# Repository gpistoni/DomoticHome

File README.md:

# DomoticHome
DomoticHome

Arduino personal Net

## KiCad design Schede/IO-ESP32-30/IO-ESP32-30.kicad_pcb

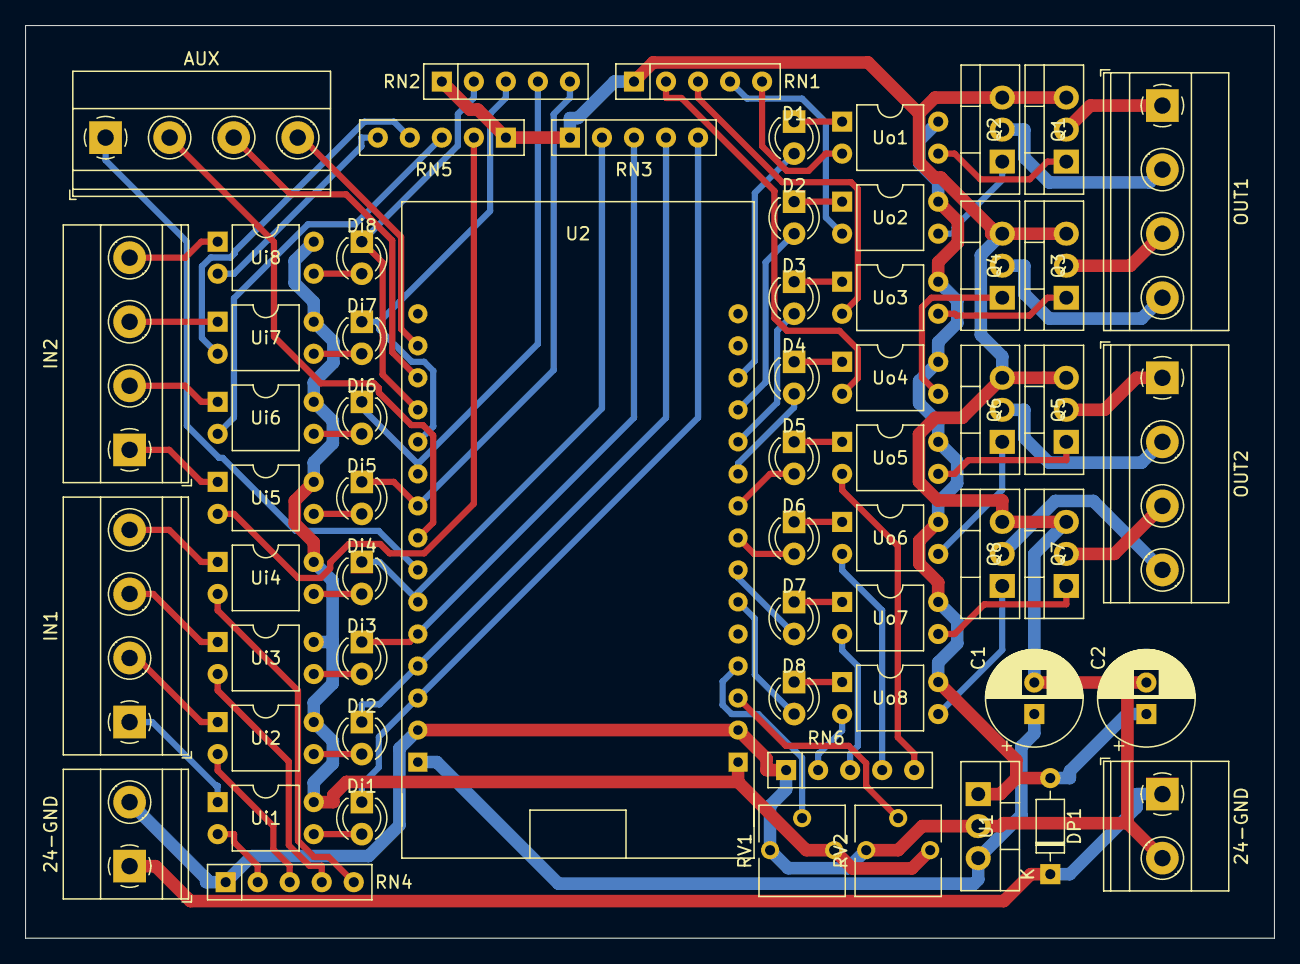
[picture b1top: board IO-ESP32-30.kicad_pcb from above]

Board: 2 copper layers, 99.1 x 72.4 mm, 60 parts (0 on the bottom side), 83 nets.

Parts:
24-GND, 24-GND#2: Screw_Terminal_01x02; TerminalBlock_Phoenix_MKDS-1,5-2-5.08_1x02_P5.08mm_Horizont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
AUX: Screw_Terminal_01x04; TerminalBlock_Phoenix_MKDS-1,5-4-5.08_1x04_P5.08mm_Horizont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
C1: 10uf; CP_Radial_D7.5mm_P2.50mm
C2: 100uf; CP_Radial_D7.5mm_P2.50mm
D1, D2, D3, D4, D5, D6, D7, D8: LED; LED_D3.0mm
DP1: DIODE; D_DO-35_SOD27_P7.62mm_Horizontal
Di1, Di2, Di3, Di4, Di5, Di6, Di7, Di8: LED; LED_D3.0mm
IN1, IN2: Screw_Terminal_01x04; TerminalBlock_Phoenix_MKDS-1,5-4-5.08_1x04_P5.08mm_Horizont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
OUT1, OUT2: Screw_Terminal_01x04; TerminalBlock_Phoenix_MKDS-1,5-4-5.08_1x04_P5.08mm_Horizont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
Q1, Q2, Q3, Q4, Q5, Q6, Q7, Q8: IRF540N; TO-220-3_Vertical
RN1, RN6: R_220; R_Array_SIP5
RN2, RN4: R_2k; R_Array_SIP5
RN3, RN5: R_1k; R_Array_SIP5
RV1, RV2: R_POT_10k; Potentiometer_Vishay_T73YP_Vertical
U1: L7805; TO-220-3_Vertical
U2: DOIT-ESP32-30PIN; ESP32-DOIT-DEVKIT
Ui1, Ui2, Ui3, Ui4, Ui5, Ui6, Ui7, Ui8: PS2501; DIP-4_W7.62mm
Uo1, Uo2, Uo3, Uo4, Uo5, Uo6, Uo7, Uo8: PS2501; DIP-4_W7.62mm

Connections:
+3V3: RV1.1, RV2.1, U2.16, Ui1.4, Ui2.4, Ui3.4, Ui4.4, Ui5.4, Ui6.4, Ui7.4, Ui8.4
+5V: C1.1, U1.3, U2.15
+24V: C2.1, DP1.2, U1.1, Uo1.4, Uo2.4, Uo3.4, Uo4.4, Uo5.4, Uo6.4, Uo7.4, Uo8.4
/P1: OUT1.1, Q1.2
/P2: OUT1.2, Q2.2
/P3: OUT1.3, Q3.2
/P4: OUT1.4, Q4.2
/P5: OUT2.1, Q5.2
/P6: OUT2.2, Q6.2
/P7: OUT2.3, Q7.2
/P8: OUT2.4, Q8.2
GND: 24-GND.2, 24-GND#2.2, C1.2, C2.2, Q1.3, Q2.3, Q3.3, Q4.3, Q5.3, Q6.3, Q7.3, Q8.3, RN1.1, RN2.1, RN3.1, RN4.1, RN5.1, RN6.1, RV1.3, RV2.3, U1.2, U2.14, U2.17
unnamed: AUX.1, U2.9
unnamed: AUX.2, U2.8
unnamed: AUX.3, U2.3
unnamed: AUX.4, U2.2
unnamed: D1.1, Uo1.1
unnamed: D1.2, U2.28
unnamed: D2.1, Uo2.1
unnamed: D2.2, U2.27
unnamed: D3.1, Uo3.1
unnamed: D3.2, U2.26
unnamed: D4.1, Uo4.1
unnamed: D4.2, U2.25
unnamed: D5.1, Uo5.1
unnamed: D5.2, U2.24
unnamed: D6.1, Uo6.1
unnamed: D6.2, U2.23
unnamed: D7.1, Uo7.1
unnamed: D7.2, U2.22
unnamed: D8.1, Uo8.1
unnamed: D8.2, U2.21
unnamed: Di1.1, RN3.5, U2.13
unnamed: Di1.2, Ui1.3
unnamed: Di2.1, RN3.4, U2.12
unnamed: Di2.2, Ui2.3
unnamed: Di3.1, RN3.3, U2.11
unnamed: Di3.2, Ui3.3
unnamed: Di4.1, RN3.2, U2.10
unnamed: Di4.2, Ui4.3
unnamed: Di5.1, RN5.5, U2.7
unnamed: Di5.2, Ui5.3
unnamed: Di6.1, RN5.4, U2.6
unnamed: Di6.2, Ui6.3
unnamed: Di7.1, RN5.3, U2.5
unnamed: Di7.2, Ui7.3
unnamed: Di8.1, RN5.2, U2.4
unnamed: Di8.2, Ui8.3
unnamed: IN1.1, Ui1.1
unnamed: IN1.2, Ui2.1
unnamed: IN1.3, Ui3.1
unnamed: IN1.4, Ui4.1
unnamed: IN2.1, Ui5.1
unnamed: IN2.2, Ui6.1
unnamed: IN2.3, Ui7.1
unnamed: IN2.4, Ui8.1
unnamed: Q1.1, Uo1.3
unnamed: Q2.1, Uo2.3
unnamed: Q3.1, Uo3.3
unnamed: Q4.1, Uo4.3
unnamed: Q5.1, Uo5.3
unnamed: Q6.1, Uo6.3
unnamed: Q7.1, Uo7.3
unnamed: Q8.1, Uo8.3
unnamed: RN1.2, Uo4.2
unnamed: RN1.3, Uo3.2
unnamed: RN1.4, Uo2.2
unnamed: RN1.5, Uo1.2
unnamed: RN2.2, Ui5.2
unnamed: RN2.3, Ui6.2
unnamed: RN2.4, Ui7.2
unnamed: RN2.5, Ui8.2
unnamed: RN4.2, Ui1.2
unnamed: RN4.3, Ui2.2
unnamed: RN4.4, Ui3.2
unnamed: RN4.5, Ui4.2
unnamed: RN6.2, Uo8.2
unnamed: RN6.3, Uo7.2
unnamed: RN6.4, Uo6.2
unnamed: RN6.5, Uo5.2
unnamed: RV1.2, U2.19
unnamed: RV2.2, U2.18
VCC: 24-GND.1, 24-GND#2.1, DP1.1

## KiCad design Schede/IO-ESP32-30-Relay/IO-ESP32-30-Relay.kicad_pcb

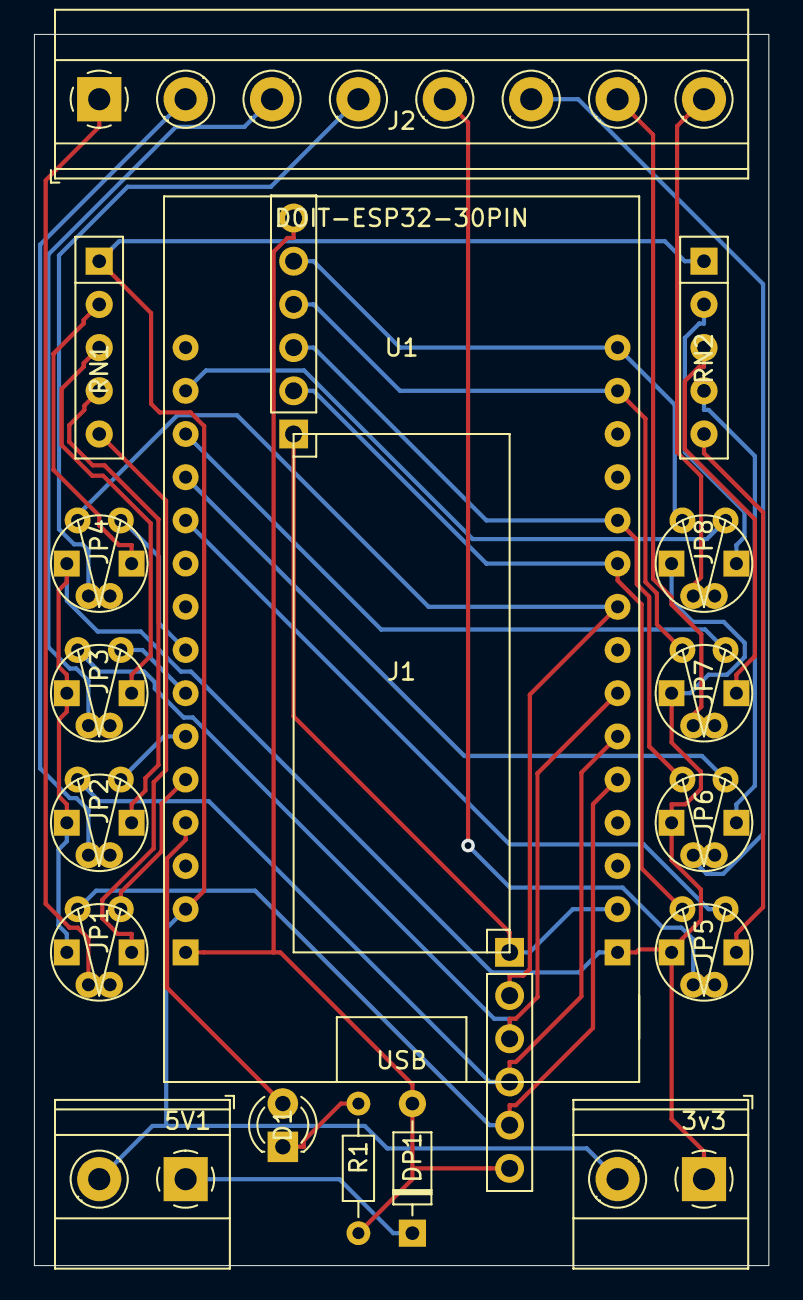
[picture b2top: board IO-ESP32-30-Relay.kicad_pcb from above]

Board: 2 copper layers, 43.2 x 72.4 mm, 18 parts (0 on the bottom side), 38 nets.

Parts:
3v3, 5V1: Screw_Terminal_01x02; TerminalBlock_Phoenix_MKDS-1,5-2-5.08_1x02_P5.08mm_Horizont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
D1: LED; LED_D3.0mm
DP1: DIODE; D_DO-35_SOD27_P7.62mm_Horizontal
J1: PinHeader_4x2Relay
J2: Screw_Terminal_01x08; TerminalBlock_Phoenix_MKDS-1,5-8-5.08_1x08_P5.08mm_Horizont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
JP1, JP2, JP3, JP4, JP5, JP6, JP7, JP8: PinHeader_3x2; PinHeader_3in2
R1: 220; R_Axial_DIN0204_L3.6mm_D1.6mm_P7.62mm_Horizontal
RN1, RN2: R_1k; R_Array_SIP5
U1: DOIT-ESP32-30PIN; ESP32-DOIT-DEVKIT

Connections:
+3V3: 3v3.1, JP1.5, JP2.5, JP3.5, JP4.5, JP5.5, JP6.5, JP7.5, JP8.5, U1.16
+5V: DP1.2, J1.1, J1.12, R1.1, U1.15
GND: 3v3.2, 5V1.2, J1.6, J1.7, RN1.1, RN2.1, U1.14, U1.17
unnamed: D1.1, R1.2
unnamed: D1.2, U1.12
unnamed: J1.2, JP8.2, U1.30
unnamed: J1.3, JP7.2, U1.29
unnamed: J1.4, JP6.2, U1.26
unnamed: J1.5, JP5.2, U1.25
unnamed: J1.8, JP4.2, U1.24
unnamed: J1.9, JP3.2, U1.22
unnamed: J1.10, JP2.2, U1.21
unnamed: J1.11, JP1.2, U1.20
unnamed: J2.1, JP1.6
unnamed: J2.2, JP2.6
unnamed: J2.3, JP3.6
unnamed: J2.4, JP4.6
unnamed: J2.5, JP5.6
unnamed: J2.6, JP6.6
unnamed: J2.7, JP7.6
unnamed: J2.8, JP8.6
unnamed: JP1.1, U1.11
unnamed: JP1.4, RN1.5
unnamed: JP2.1, U1.10
unnamed: JP2.4, RN1.4
unnamed: JP3.1, U1.9
unnamed: JP3.4, RN1.3
unnamed: JP4.1, U1.8
unnamed: JP4.4, RN1.2
unnamed: JP5.1, U1.5
unnamed: JP5.4, RN2.5
unnamed: JP6.1, U1.4
unnamed: JP6.4, RN2.4
unnamed: JP7.1, U1.3
unnamed: JP7.4, RN2.3
unnamed: JP8.1, U1.2
unnamed: JP8.4, RN2.2
VCC: 5V1.1, DP1.1

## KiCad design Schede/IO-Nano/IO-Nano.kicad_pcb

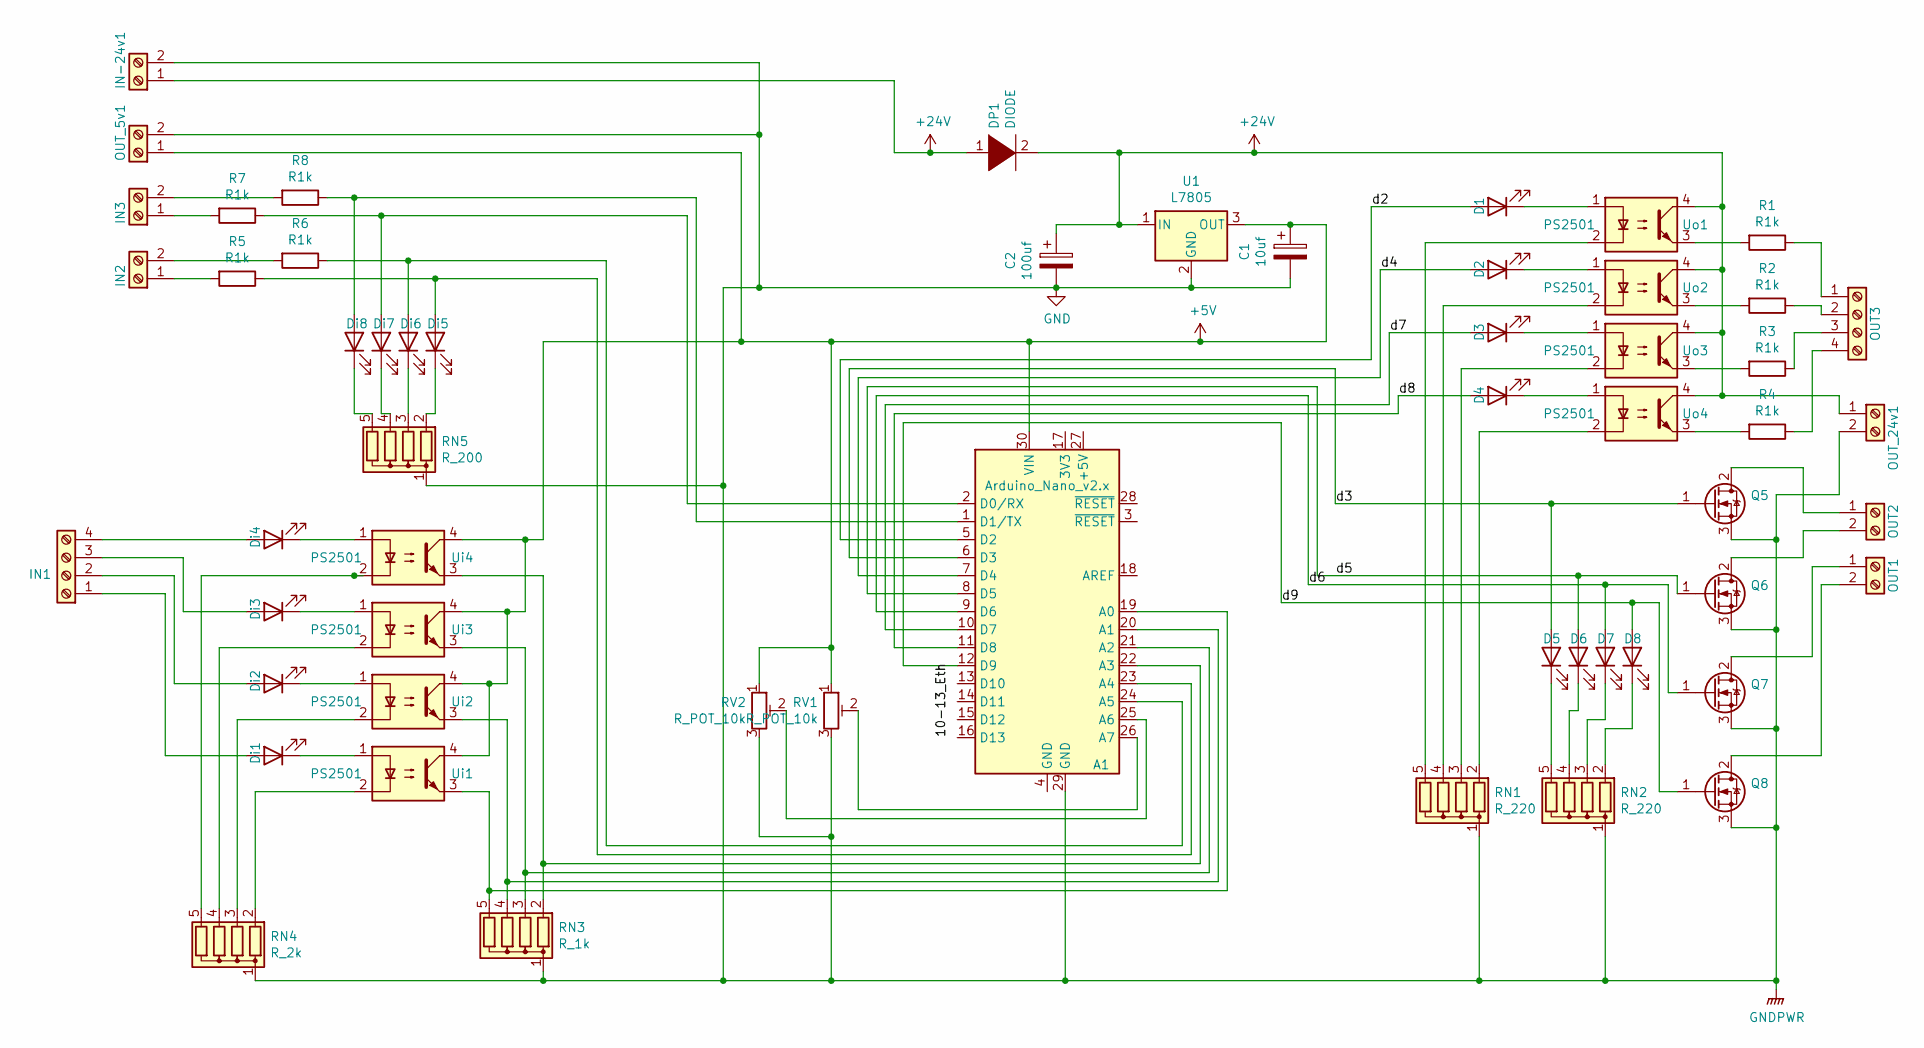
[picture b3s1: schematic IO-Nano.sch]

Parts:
A1: Arduino_Nano_v2.x; Arduino_Nano
C1: 10uf; CP_Radial_D7.5mm_P2.50mm
C2: 100uf; CP_Radial_D7.5mm_P2.50mm
D1, D2, D3, D4, D5, D6, D7, D8: LED; LED_D3.0mm
DP1: DIODE; D_DO-35_SOD27_P7.62mm_Horizontal
Di1, Di2, Di3, Di4, Di5, Di6, Di7, Di8: LED; LED_D3.0mm
IN1: Screw_Terminal_01x04; TerminalBlock_Phoenix_MKDS-1,5-4-5.08_1x04_P5.08mm_Horizont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
IN2, IN3: Screw_Terminal_01x02; TerminalBlock_Phoenix_MKDS-1,5-2-5.08_1x02_P5.08mm_Horizont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
IN-24v1: Screw_Terminal_01x02; TerminalBlock_Phoenix_MKDS-1,5-2-5.08_1x02_P5.08mm_Horizont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
OUT1, OUT2: Screw_Terminal_01x02; TerminalBlock_Phoenix_MKDS-1,5-2-5.08_1x02_P5.08mm_Horizont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
OUT3: Screw_Terminal_01x04; TerminalBlock_Phoenix_MKDS-1,5-4-5.08_1x04_P5.08mm_Horizont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
OUT_5v1, OUT_24v1: Screw_Terminal_01x02; TerminalBlock_Phoenix_MKDS-1,5-2-5.08_1x02_P5.08mm_Horizont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
Q5, Q6, Q7, Q8: IRF540N; TO-220-3_Vertical
R1, R2, R3, R4, R5, R6, R7, R8: R1k; R_Axial_DIN0204_L3.6mm_D1.6mm_P7.62mm_Horizontal
RN1, RN2: R_220; R_Array_SIP5
RN3: R_1k; R_Array_SIP5
RN4: R_2k; R_Array_SIP5
RN5: R_200; R_Array_SIP5
RV1, RV2: R_POT_10k; Potentiometer_Vishay_T73YP_Vertical
U1: L7805; TO-220-3_Vertical
Ui1, Ui2, Ui3, Ui4: PS2501; DIP-4_W7.62mm
Uo1, Uo2, Uo3, Uo4: PS2501; DIP-4_W7.62mm

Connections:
+5V: A1.30 (VIN), C1.1, OUT_5v1.1, RV1.1, RV2.1, U1.3 (OUT), Ui1.4, Ui2.4, Ui3.4, Ui4.4
+24V: C2.1, DP1.1 (K), DP1.2 (A), IN-24v1.1, OUT_24v1.1, U1.1 (IN), Uo1.4, Uo2.4, Uo3.4, Uo4.4
/d2: A1.5 (D2), D1.2 (A)
/d3: A1.6 (D3), D5.2 (A), Q5.1 (G)
/d4: A1.7 (D4), D2.2 (A)
/d5: A1.8 (D5), D6.2 (A), Q6.1 (G)
/d6: A1.9 (D6), D7.2 (A), Q7.1 (G)
/d7: A1.10 (D7), D3.2 (A)
/d8: A1.11 (D8), D4.2 (A)
/d9: A1.12 (D9), D8.2 (A), Q8.1 (G)
GND: A1.29 (GND), C1.2, C2.2, IN-24v1.2, OUT_5v1.2, OUT_24v1.2, Q5.3 (S), Q6.3 (S), Q7.3 (S), Q8.3 (S), RN1.1 (common), RN2.1 (common), RN3.1 (common), RN4.1 (common), RN5.1 (common), RV1.3, RV2.3, U1.2 (GND)
unnamed: A1.1 (D1/TX), Di8.2 (A), R8.1
unnamed: A1.2 (D0/RX), Di7.2 (A), R7.1
unnamed: A1.19 (A0), RN3.5 (R4), Ui1.3
unnamed: A1.20 (A1), RN3.4 (R3), Ui2.3
unnamed: A1.21 (A2), RN3.3 (R2), Ui3.3
unnamed: A1.22 (A3), RN3.2 (R1), Ui4.3
unnamed: A1.23 (A4), Di5.2 (A), R5.1
unnamed: A1.24 (A5), Di6.2 (A), R6.1
unnamed: A1.25 (A6), RV2.2
unnamed: A1.26 (A7), RV1.2
unnamed: D1.1 (K), Uo1.1
unnamed: D2.1 (K), Uo2.1
unnamed: D3.1 (K), Uo3.1
unnamed: D4.1 (K), Uo4.1
unnamed: D5.1 (K), RN2.5 (R4)
unnamed: D6.1 (K), RN2.4 (R3)
unnamed: D7.1 (K), RN2.3 (R2)
unnamed: D8.1 (K), RN2.2 (R1)
unnamed: Di1.1 (K), Ui1.1
unnamed: Di1.2 (A), IN1.1
unnamed: Di2.1 (K), Ui2.1
unnamed: Di2.2 (A), IN1.2
unnamed: Di3.1 (K), Ui3.1
unnamed: Di3.2 (A), IN1.3
unnamed: Di4.1 (K), Ui4.1
unnamed: Di4.2 (A), IN1.4
unnamed: Di5.1 (K), RN5.2 (R1)
unnamed: Di6.1 (K), RN5.3 (R2)
unnamed: Di7.1 (K), RN5.4 (R3)
unnamed: Di8.1 (K), RN5.5 (R4)
unnamed: IN2.1, R5.2
unnamed: IN2.2, R6.2
unnamed: IN3.1, R7.2
unnamed: IN3.2, R8.2
unnamed: OUT1.1, Q7.2 (D)
unnamed: OUT1.2, Q8.2 (D)
unnamed: OUT2.1, Q5.2 (D)
unnamed: OUT2.2, Q6.2 (D)
unnamed: OUT3.1, R1.1
unnamed: OUT3.2, R2.1
unnamed: OUT3.3, R3.1
unnamed: OUT3.4, R4.1
unnamed: R1.2, Uo1.3
unnamed: R2.2, Uo2.3
unnamed: R3.2, Uo3.3
unnamed: R4.2, Uo4.3
unnamed: RN1.2 (R1), Uo4.2
unnamed: RN1.3 (R2), Uo3.2
unnamed: RN1.4 (R3), Uo2.2
unnamed: RN1.5 (R4), Uo1.2
unnamed: RN4.2 (R1), Ui1.2
unnamed: RN4.3 (R2), Ui2.2
unnamed: RN4.4 (R3), Ui3.2
unnamed: RN4.5 (R4), Ui4.2

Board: 2 copper layers, 57 parts (0 on the bottom side), 65 nets, no tracks yet.

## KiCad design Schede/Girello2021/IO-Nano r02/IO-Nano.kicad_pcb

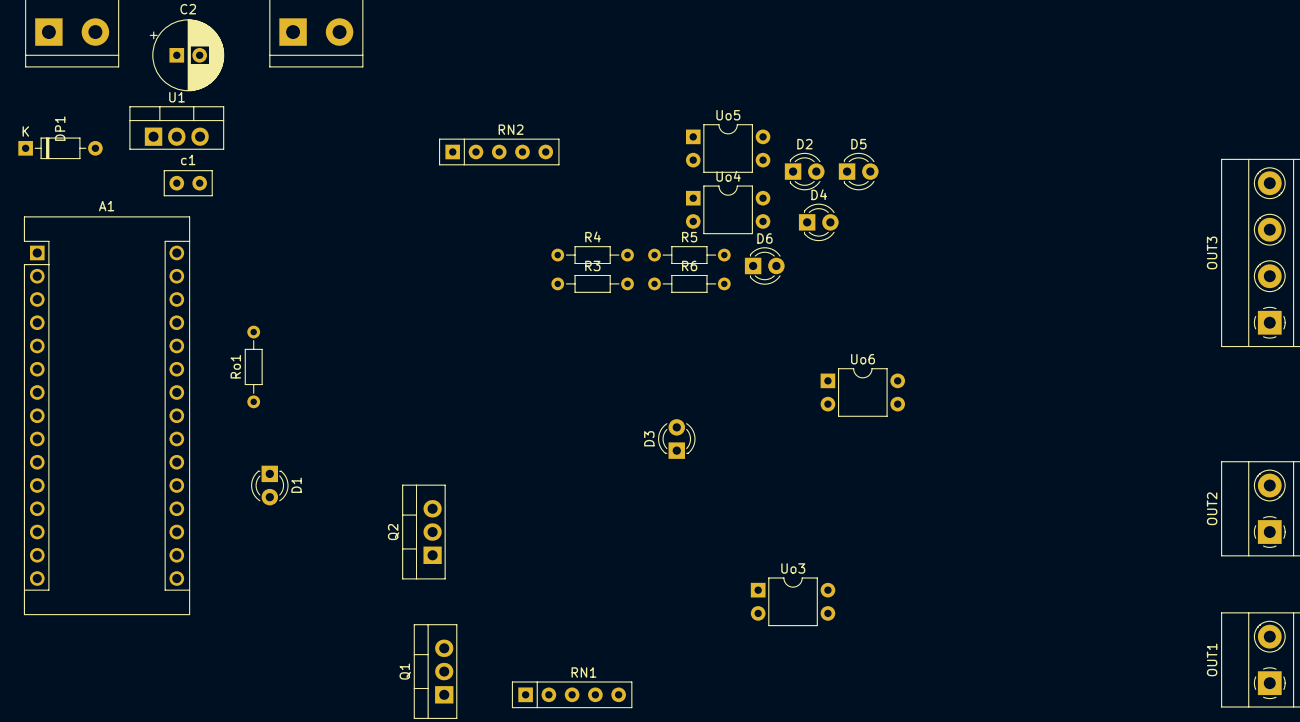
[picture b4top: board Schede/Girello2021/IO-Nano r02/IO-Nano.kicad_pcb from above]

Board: 2 copper layers, 29 parts (0 on the bottom side), 28 nets, no tracks yet.

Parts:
5v-GND1, 24v-GND1: Screw_Terminal_01x02; TerminalBlock_bornier-2_P5.08mm
A1: Arduino_Nano_v2.x; Arduino_Nano
C2: 10uf; CP_Radial_D7.5mm_P2.50mm
D1, D2, D3, D4, D5, D6: LED; LED_D3.0mm
DP1: DIODE; D_DO-35_SOD27_P7.62mm_Horizontal
OUT1, OUT2: Screw_Terminal_01x02; TerminalBlock_Phoenix_MKDS-1,5-2-5.08_1x02_P5.08mm_Horizont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
OUT3: Screw_Terminal_01x04; TerminalBlock_Phoenix_MKDS-1,5-4-5.08_1x04_P5.08mm_Horizont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
Q1, Q2: IRF540N; TO-220-3_Vertical
R3, R4, R5, R6: R1k; R_Axial_DIN0204_L3.6mm_D1.6mm_P7.62mm_Horizontal
RN1, RN2: R_220; R_Array_SIP5
Ro1: R220; R_Axial_DIN0204_L3.6mm_D1.6mm_P7.62mm_Horizontal
U1: L7805; TO-220-3_Vertical
Uo3, Uo4, Uo5, Uo6: PS2501; DIP-4_W7.62mm
c1: 100nF; C_Disc_D5.0mm_W2.5mm_P2.50mm

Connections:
+5V: 5v-GND1.1, A1.30, U1.3, c1.2
+24V: C2.1, DP1.2, U1.1, Uo3.4, Uo4.4, Uo5.4, Uo6.4
GND: 5v-GND1.2, 24v-GND1.2, A1.29, C2.2, RN1.1, RN2.1, RN2.2, Ro1.2, U1.2, c1.1
unnamed: 24v-GND1.1, DP1.1
unnamed: A1.5, D6.2, Uo6.1
unnamed: A1.6, D5.2, Uo5.1
unnamed: A1.7, D4.2, Uo4.1
unnamed: A1.8, D2.2, Q2.1
unnamed: A1.9, D1.2, Q1.1
unnamed: A1.10, D3.2, Uo3.1
unnamed: D1.1, Ro1.1
unnamed: D2.1, RN2.5
unnamed: D3.1, RN1.2, Uo3.2
unnamed: D4.1, RN1.3, Uo4.2
unnamed: D5.1, RN1.4, Uo5.2
unnamed: D6.1, RN1.5, Uo6.2
unnamed: OUT1.1, Q1.2
unnamed: OUT1.2, Q1.3
unnamed: OUT2.1, Q2.2
unnamed: OUT2.2, Q2.3
unnamed: OUT3.1, R6.1
unnamed: OUT3.2, R5.1
unnamed: OUT3.3, R4.1
unnamed: OUT3.4, R3.1
unnamed: R3.2, Uo3.3
unnamed: R4.2, Uo4.3
unnamed: R5.2, Uo5.3
unnamed: R6.2, Uo6.3

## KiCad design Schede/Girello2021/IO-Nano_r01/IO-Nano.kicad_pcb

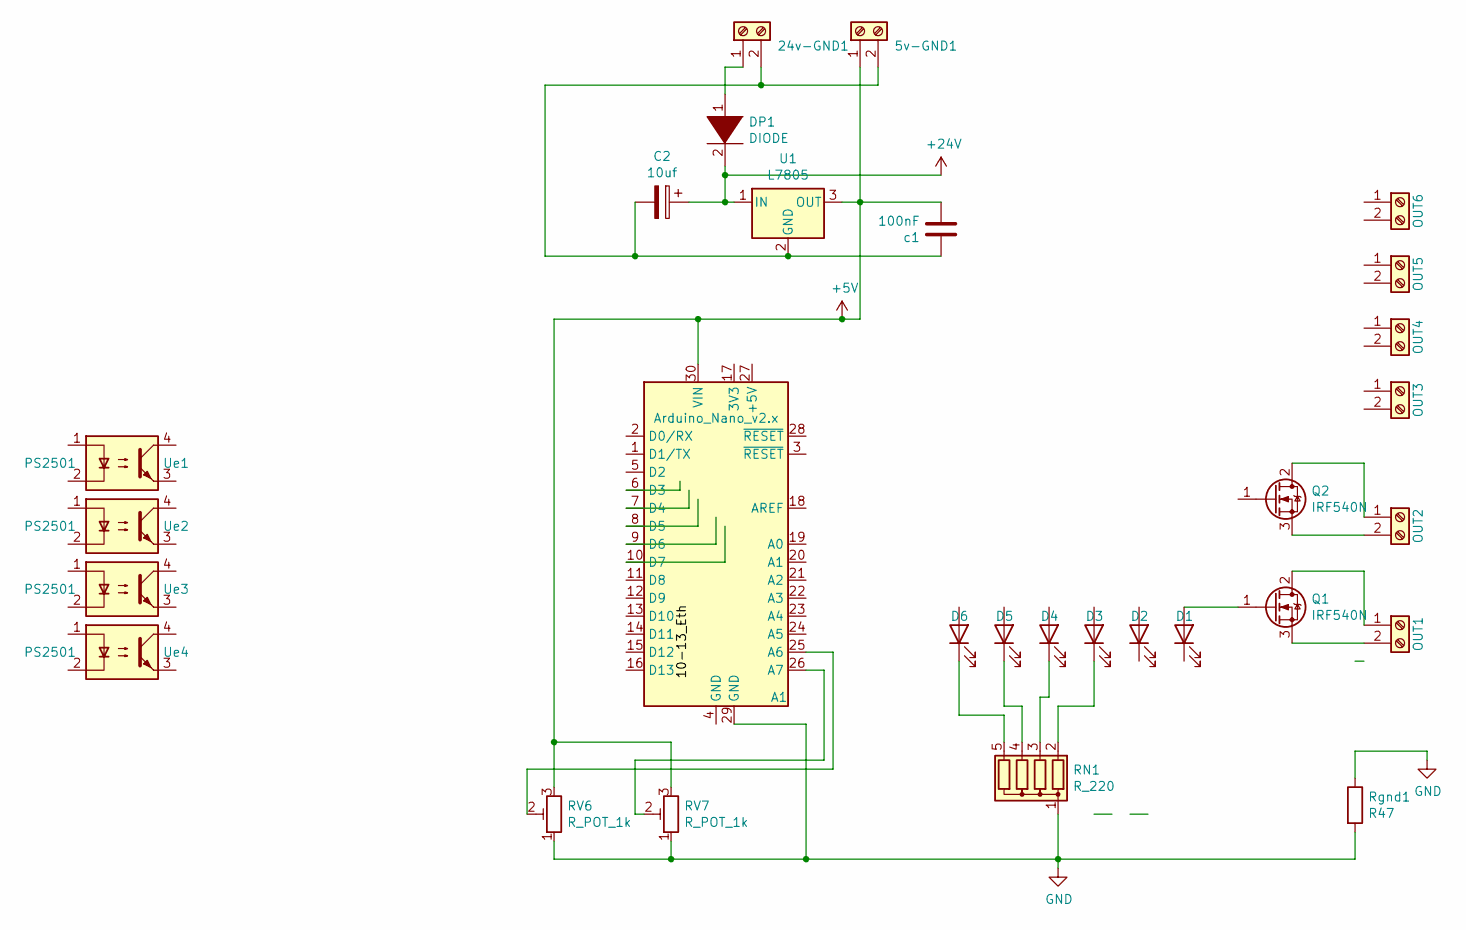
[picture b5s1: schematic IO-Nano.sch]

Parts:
5v-GND1, 24v-GND1: Screw_Terminal_01x02; TerminalBlock_Phoenix_MKDS-1,5-2-5.08_1x02_P5.08mm_Horizont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
A1: Arduino_Nano_v2.x; Arduino_Nano
C2: 10uf; CP_Radial_D7.5mm_P2.50mm
D1, D2, D3, D4, D5, D6: LED; LED_D3.0mm
DP1: DIODE; D_DO-35_SOD27_P7.62mm_Horizontal
OUT1, OUT2, OUT4, OUT6: Screw_Terminal_01x02; TerminalBlock_Phoenix_MKDS-1,5-2-5.08_1x02_P5.08mm_Horizont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
OUT3, OUT5: Screw_Terminal_01x02; TerminalBlock_bornier-2_P5.08mm
Q1, Q2: IRF540N; TO-220-3_Vertical
RN1: R_220; R_Array_SIP5
RV6, RV7: R_POT_1k; Potentiometer_Vishay_T73YP_Vertical
Rgnd1: R47; R_Axial_DIN0204_L3.6mm_D1.6mm_P7.62mm_Horizontal
U1: L7805; TO-220-3_Vertical
Ue1, Ue2, Ue3, Ue4: PS2501; DIP-4_W7.62mm
c1: 100nF; C_Disc_D5.0mm_W2.5mm_P2.50mm

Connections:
+5V: 5v-GND1.1, A1.30 (VIN), RV6.3, RV7.3, U1.3 (OUT), c1.2
+24V: C2.1, DP1.2 (A), U1.1 (IN)
GND: A1.29 (GND), RN1.1 (common), RV6.1, RV7.1, Rgnd1.1, Rgnd1.2; also elsewhere on the board
unnamed: 24v-GND1.1, DP1.1 (K)
unnamed: 5v-GND1.2, 24v-GND1.2, C2.2, U1.2 (GND), c1.1
unnamed: A1.25 (A6), RV6.2
unnamed: A1.26 (A7), RV7.2
unnamed 33: D1.1 (K); also elsewhere on the board
unnamed: D1.2 (A), Q1.1 (G)
unnamed: D3.1 (K), RN1.2 (R1)
unnamed: D4.1 (K), RN1.3 (R2)
unnamed: D5.1 (K), RN1.4 (R3)
unnamed: D6.1 (K), RN1.5 (R4)
unnamed: OUT1.1, Q1.2 (D)
unnamed: OUT1.2, Q1.3 (S)
unnamed: OUT2.1, Q2.2 (D)
unnamed: OUT2.2, Q2.3 (S)

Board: 2 copper layers, 30 parts (0 on the bottom side), 17 nets, no tracks yet.

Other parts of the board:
Ro1: R220; R_Axial_DIN0204_L3.6mm_D1.6mm_P7.62mm_Horizontal

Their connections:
GND: Ro1.2; also elsewhere on the board
unnamed 33: Ro1.1; also elsewhere on the board

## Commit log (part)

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2015-09-21 webserver
2015-09-25 test socket web desktop remoto funzionate
2015-09-28 http
2015-09-30 supervisor
2015-10-02 histogram
2015-10-10 Home
2015-10-10 qres
2015-10-14 value set param
2015-10-18 web servr
2015-10-21 adafruit
2015-10-27 httpserver nuovo
2015-10-28 DataTable
2015-10-31 dhconfig
2015-11-08 updated libraries
2015-12-21 crc added
2016-01-09 updated 1.6.6 new web server
2016-01-18 http server
2016-01-27 dataTemp +-
2016-02-10 temp media
2016-02-26 joystik
2016-02-27 cambio joystik
2016-03-11 web server
2016-03-13 risolto guasto server
2016-03-13 json
2016-04-26 programmi
2016-06-26 summerEco
2016-07-31 summer AC
2016-10-09 gestione programmi winter / summer
2016-10-13 rolling set vaue
2016-10-14 risolti problemi winter
2016-10-23 risolto bug
2016-11-05 r Changes to be committed: r
2016-11-05 term 4
2016-11-05 light
2016-11-19 baco for fuori limite dhtprotocol
2016-11-20 deleted
2016-11-20 rimosse librerie std
2016-11-20 light external
2016-11-22 HTTPSRedirect
2016-11-28 christmas
2016-12-04 slave 2 light
2016-12-05 lamp
2016-12-23 boileracs
2017-01-07 terminal2
2017-01-11 google docs
2017-01-15 https script google
2017-01-21 googlescript
2017-01-29 googledata
2017-02-04 google script
2017-02-06 googledata2app
2017-02-15 static./arduino-1.8.1/arduino
2017-06-24 ac manager summer
2017-08-02 summer
2017-08-05 Changed subnet
2017-08-08 wifi page1.html
2017-11-21 Cella di Carico
2017-12-14 usbjpystik
2017-12-16 wrong_ip
2017-12-31 Amperometro casa
2018-01-05 Aggiunto modulo6 amperometri
2018-01-25 Amperometri
2018-02-01 ajax
2018-02-01 ImageTransfer
2018-02-05 test joystik
2018-02-12 t camino
2018-02-22 bug_ev
2018-03-24 sistemati manager - Rimosso AP nodeMCU
2018-03-25 aggiornamneto casa
2018-03-30 RaceSeat
2018-04-03 ajaxtest
2018-04-08 light ext
2018-04-17 test ajax json
2018-04-17 qt json server
2018-06-22 modificato soglia luci esterne
2018-07-31 night mode
2018-10-21 Fotovltaico
2018-11-11 json server
2018-11-18 comunicazione server-supervisor get set json
2018-11-21 QT client server
2018-11-24 test qt
2018-12-01 button
2018-12-02 infovar
2018-12-05 setpoint
2018-12-11 termial 6
2018-12-29 duplicato progetto
2019-02-07 server pdc
2019-06-16 SummerAC
2019-06-18 Unificatowinter-summerpdc
2019-06-19 log su file con ora
2019-06-23 1.1.2
2019-06-27 regolazione summerAC
2019-07-05 1.1.3
2019-08-04 aggiornato arduino 1.8.5
2019-08-08 manage internet
2019-08-10 server SONOFF internet
2019-08-11 sonoff
2019-09-22 sonoff_nOn
2019-09-22 1.2.2
2019-10-06 dbevents
2019-10-13 removed .o
2019-11-04 pumps
2019-11-26 server 1.4.0
2019-11-26 android
2019-12-11 remote 212
2019-12-11 pistonihome2
2020-01-02 1.5.0
2020-01-15 build android
2020-03-10 camperaplc
2020-03-23 cameraplc
2020-05-16 internet timer
2020-06-26 estate
2020-09-26 1.6.6
2020-10-17 winter
2020-11-19 1.7.0
2020-12-05 1.7.1
2020-12-26 internet
2021-02-06 server
2021-02-10 girello2021
    girello2021
2021-02-11 nanor1 - windows
2021-02-17 esp32
2021-02-18 _LibKicad folder
2021-02-19 esp32.pcb
2021-02-22 relay
2021-03-10 Dashboard
2021-03-10 update libraries
2021-03-10 server 1.8
2021-03-14 httprequest php site
2021-03-15 addrow
2021-03-15 db php
2021-03-17 bootstrap
2021-03-17 Data Query insert table
2021-03-19 dbmanager
2021-03-19 database.php
2021-03-22 cprobe crelay
2021-03-22 set.php
2021-03-23 fullpower
2021-03-24 energia luci.php
2021-03-28 onewire
2021-04-07 luci
2021-04-07 wattage chart
2021-04-11 chart
2021-06-28 timing
2021-08-15 Watchdog
    Watchdog
2021-08-15 Watchdog
2021-09-27 freezer
2021-11-20 webDB
2021-11-28 christmas-light
2021-12-06 token
2021-12-07 natale
2022-05-28 maggio e estate
2023-01-31 camino
